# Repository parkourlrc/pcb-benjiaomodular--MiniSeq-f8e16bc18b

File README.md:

# MiniSeq
[![CC BY-SA 4.0][cc-by-sa-shield]][cc-by-sa]

Full docs on my website: https://benjiaomodular.com/post/miniseq/

This is my second time building a Baby-8 step CV sequencer since my [plexiglass Baby-8 build](https://benjiaomodular.com/post/2021-04-09-8-step-sequencer) from two years ago. This, time I added a gate output, a reset input, and a step length control.

## Schematics

## License

This work is licensed under a
[Creative Commons Attribution-ShareAlike 4.0 International License][cc-by-sa].

[![CC BY-SA 4.0][cc-by-sa-image]][cc-by-sa]

[cc-by-sa]: http://creativecommons.org/licenses/by-sa/4.0/
[cc-by-sa-image]: https://licensebuttons.net/l/by-sa/4.0/88x31.png
[cc-by-sa-shield]: https://img.shields.io/badge/License-CC%20BY--SA%204.0-lightgrey.svg

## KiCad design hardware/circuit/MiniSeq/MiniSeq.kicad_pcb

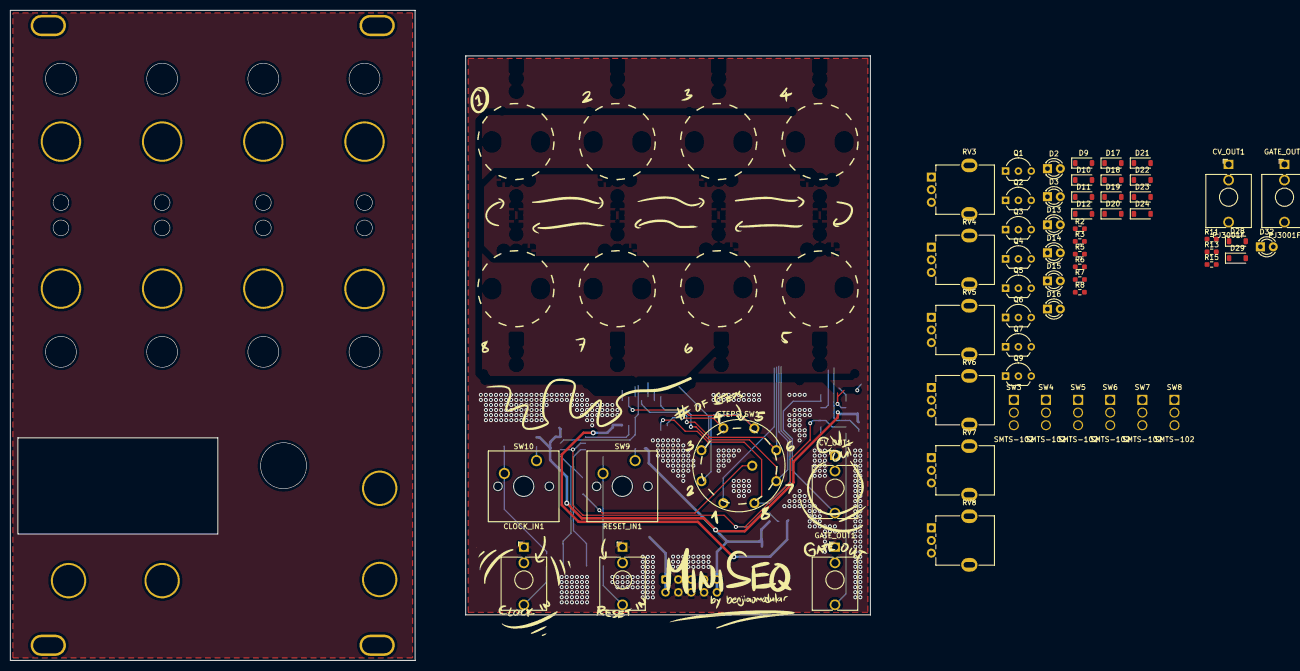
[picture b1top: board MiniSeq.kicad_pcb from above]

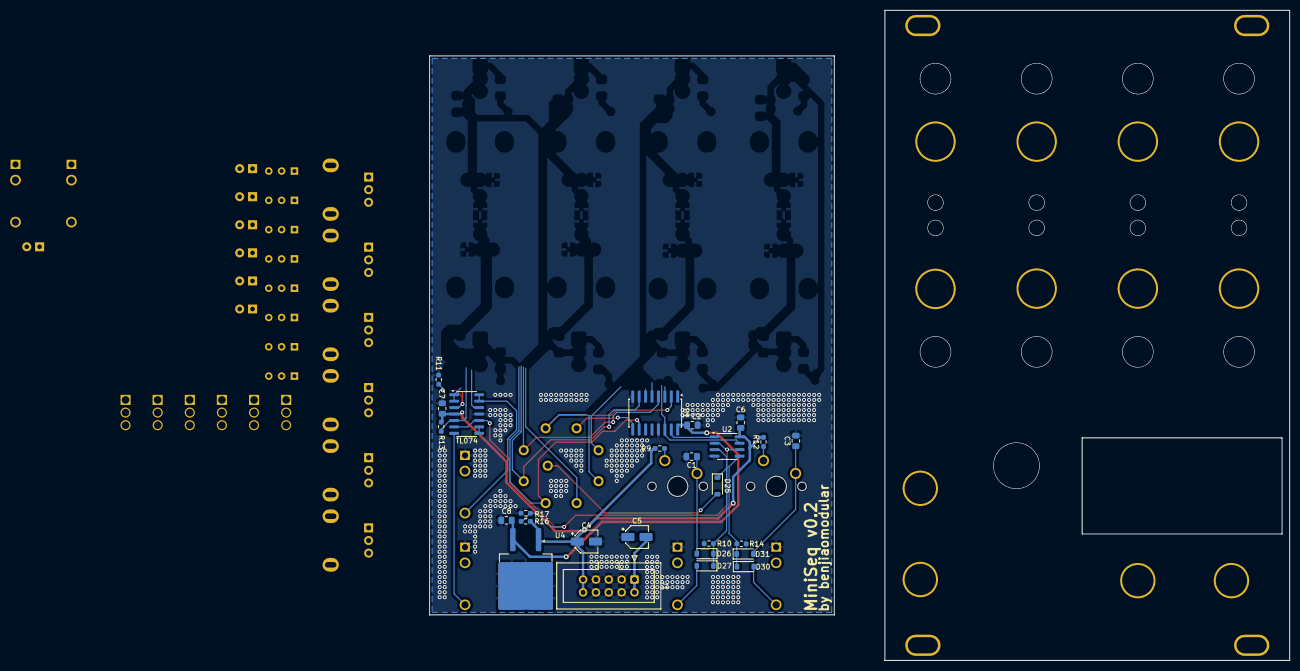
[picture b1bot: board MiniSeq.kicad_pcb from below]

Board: 2 copper layers, 170.0 x 128.5 mm, 85 parts (26 on the bottom side), 57 nets.

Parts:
C1, C2, C3, C6, C7: 100nF; C_0805_2012Metric_Pad1.18x1.45mm_HandSolder
C4, C5: 22uF; CP_Elec_4x3.9
C8: 10uF; C_0805_2012Metric_Pad1.18x1.45mm_HandSolder
CLOCK_IN1: PJ3001F; AudioJack_3.5mm
CV_OUT1, CV_OUT1#2: PJ3001F; AudioJack_3.5mm
D2, D3, D13, D14, D15, D16, D32: LED; LED_D3.0mm
D9, D10, D11, D12, D17, D18, D19, D20, D21, D22, D23, D24, D25, D26, D27, D28, D29, D30, D31: 1N4148; D_SOD-123
GATE_OUT1, GATE_OUT1#2: PJ3001F; AudioJack_3.5mm
J1: Conn_01x10_Pin; IDC-Header_2x05_P2.54mm_Vertical
Q1, Q2, Q3, Q4, Q5, Q6, Q7, Q9: BC547; TO-92_Inline_Wide
R2, R3, R5, R6, R7, R8, R9, R12, R15: 10k; R_0603_1608Metric_Pad0.98x0.95mm_HandSolder
R10, R11, R11#2, R13, R13#2, R14, R16: 100k; R_0603_1608Metric_Pad0.98x0.95mm_HandSolder
R17: 33k; R_0603_1608Metric_Pad0.98x0.95mm_HandSolder
RESET_IN1: PJ3001F; AudioJack_3.5mm
RV3, RV4, RV5, RV6, RV7, RV8: B100k; Potentiometer_RV09
STEPS_SW1: RotarySwitch_SR16_POLE1_WAY8
SW3, SW4, SW5, SW6, SW7, SW8: SMTS-102; ToggleSwitch_SMTS-102
SW9: RESET_BTN; SW_Cherry_MX_1.00u_PCB
SW10: CLOCK_BTN; SW_Cherry_MX_1.00u_PCB
U1: 4017; SOIC-16W_5.3x10.2mm_P1.27mm
U2: TL072; SOIC-8_3.9x4.9mm_P1.27mm
U3: TL074; SOIC-14_3.9x8.7mm_P1.27mm
U4: L7809CD2T-TR; TO-263-2

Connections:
+9V: C2.1, C8.1, Q1.1 (C), Q2.1 (C), Q3.1 (C), Q4.1 (C), Q5.1 (C), Q6.1 (C), Q7.1 (C), Q9.1 (C), U1.16 (VDD), U4.3 (OUT)
+12V: C4.1, C6.1, C7.1, J1.9, J1.10, R9.2, R12.2, R13.1, R13#2.1, R16.1, U2.8 (V+), U3.4 (V+), U4.1 (IN)
-12V: C5.2, J1.1, J1.2
/CLOCK: U1.14 (CLK), U2.7
/RESET: U1.15 (Reset), U2.1
/STEP1: Q9.2 (B), U1.3 (Q0)
/STEP2: Q1.2 (B), STEPS_SW1.1, U1.2 (Q1)
/STEP3: Q2.2 (B), R2.2, STEPS_SW1.2, SW3.2 (B), U1.4 (Q2)
/STEP4: Q3.2 (B), R3.2, STEPS_SW1.3, SW4.2 (B), U1.7 (Q3)
/STEP5: Q4.2 (B), R8.2, STEPS_SW1.4, SW5.2 (B), U1.10 (Q4)
/STEP6: Q5.2 (B), R5.2, STEPS_SW1.5, SW6.2 (B), U1.1 (Q5)
/STEP7: Q6.2 (B), R6.2, STEPS_SW1.6, SW7.2 (B), U1.5 (Q6)
/STEP8: Q7.2 (B), R7.2, STEPS_SW1.7, SW8.2 (B), U1.6 (Q7)
/STEP9: STEPS_SW1.8, U1.9 (Q8)
CV_OUT: D10.1 (K), D12.1 (K), D18.1 (K), D20.1 (K), D22.1 (K), D24.1 (K), U3.12 (+)
GATE_OUT: D9.1 (K), D11.1 (K), D17.1 (K), D19.1 (K), D21.1 (K), D23.1 (K), R11.2, R11#2.2, U3.3 (+)
GND: C1.2, C2.2, C3.2, C4.2, C5.1, C6.2, C7.2, C8.2, CLOCK_IN1.S, CV_OUT1.S, CV_OUT1#2.S, D2.1 (K), D3.1 (K), D13.1 (K), D14.1 (K), D15.1 (K), D16.1 (K), GATE_OUT1.S, GATE_OUT1#2.S, J1.3, J1.4, J1.5, J1.6, J1.7, J1.8, R10.2, R11.1, R11#2.1, R14.1, R15.2, R17.2, RESET_IN1.S, RV3.1, RV4.1, RV5.1, RV6.1, RV7.1, RV8.1, U1.8 (VSS), U1.13 (CKEN), U2.4 (V-), U3.11 (V-), U4.2 (GND)
unnamed: D2.2 (A), R2.1
unnamed: D3.2 (A), R3.1
unnamed: D9.2 (A), SW3.1 (A)
unnamed: D10.2 (A), RV3.2
unnamed: D11.2 (A), SW4.1 (A)
unnamed: D12.2 (A), RV4.2
unnamed: D13.2 (A), R5.1
unnamed: D14.2 (A), R6.1
unnamed: D15.2 (A), R7.1
unnamed: D16.2 (A), R8.1
unnamed: D17.2 (A), SW5.1 (A)
unnamed: D18.2 (A), RV5.2
unnamed: D19.2 (A), SW6.1 (A)
unnamed: D20.2 (A), RV6.2
unnamed: D21.2 (A), SW7.1 (A)
unnamed: D22.2 (A), RV7.2
unnamed: D23.2 (A), SW8.1 (A)
unnamed: D24.2 (A), RV8.2
unnamed: D25.2 (A), STEPS_SW1.9
unnamed: D25.1 (K), D26.1 (K), D27.1 (K), R10.1, U2.3 (+)
unnamed: C1.1, D26.2 (A), SW9.2
unnamed: D27.2 (A), RESET_IN1.T
unnamed: D28.2 (A), D29.2 (A), R13.2, R13#2.2, U3.5 (+)
unnamed: D29.1 (K), U3.1, U3.2 (-)
unnamed: CLOCK_IN1.T, D30.2 (A)
unnamed: D30.1 (K), D31.1 (K), R14.2, U2.5 (+)
unnamed: C3.1, D31.2 (A), SW10.2
unnamed: D32.2 (A), GATE_OUT1.T, U3.7
unnamed: D32.1 (K), R15.1
unnamed: Q2.3 (E), RV3.3
unnamed: Q3.3 (E), RV4.3
unnamed: Q4.3 (E), RV5.3
unnamed: Q5.3 (E), RV6.3
unnamed: Q6.3 (E), RV7.3
unnamed: Q7.3 (E), RV8.3
unnamed: R9.1, SW9.1
unnamed: R12.1, SW10.1
unnamed: U3.8, U3.9 (-)
unnamed: CV_OUT1.T, CV_OUT1#2.T, U3.13 (-), U3.14
VREF: R16.2, R17.1, U2.2 (-), U2.6 (-), U3.6 (-), U3.10 (+)

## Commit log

2024-11-12 Added bom
2024-12-16 Updated schematics
